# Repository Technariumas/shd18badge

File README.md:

# Science Hack Day Vilnius 2018 - badge

Participant badge for Science Hack Day Vilnius 2018

## Prerequisites

To use the badge, you will need the following:

 * A laptop with Linux, Mac OS or Windows and at least one free USB port.
 * If it’s Windows or Mac OS, make sure to install [drivers](https://wiki.wemos.cc/downloads) for the CH340 UBS2TTL chip.
 * A micro-USB cable with data lines that fits your USB port.
 * You will need a terminal application installed. For Linux and Mac you can use screen, which is installed by default. For Windows we recommend [PuTTy](http://www.chiark.greenend.org.uk/~sgtatham/putty/download.html) or [CoolTerm](http://freeware.the-meiers.org/).
 * Please note that the workshop will be in English.

## Schematics

## Programming

Use dmesg to determine the USB port the badge is connected to, e.g. /dev/ttyUSB0.

Flash the firmware:
cd shd18badge/micropython

Edit the flash_microcontroller.sh file so that it points to the correct USB port. If esptool.py is needed, install it (for example, pip install esptool.py). Then copy the Python files to the microcontroller:

python transfer_files.py -p /dev/ttyUSB5 -b 115200 util.py main.py thermistor.py boot.py
 
## Tutorial
 * A pretty great [tutorial is available here](http://docs.micropython.org/en/latest/esp8266/esp8266/tutorial/index.html)
 * [A MAC user first hand experience](MACUSERS.md) using the badge

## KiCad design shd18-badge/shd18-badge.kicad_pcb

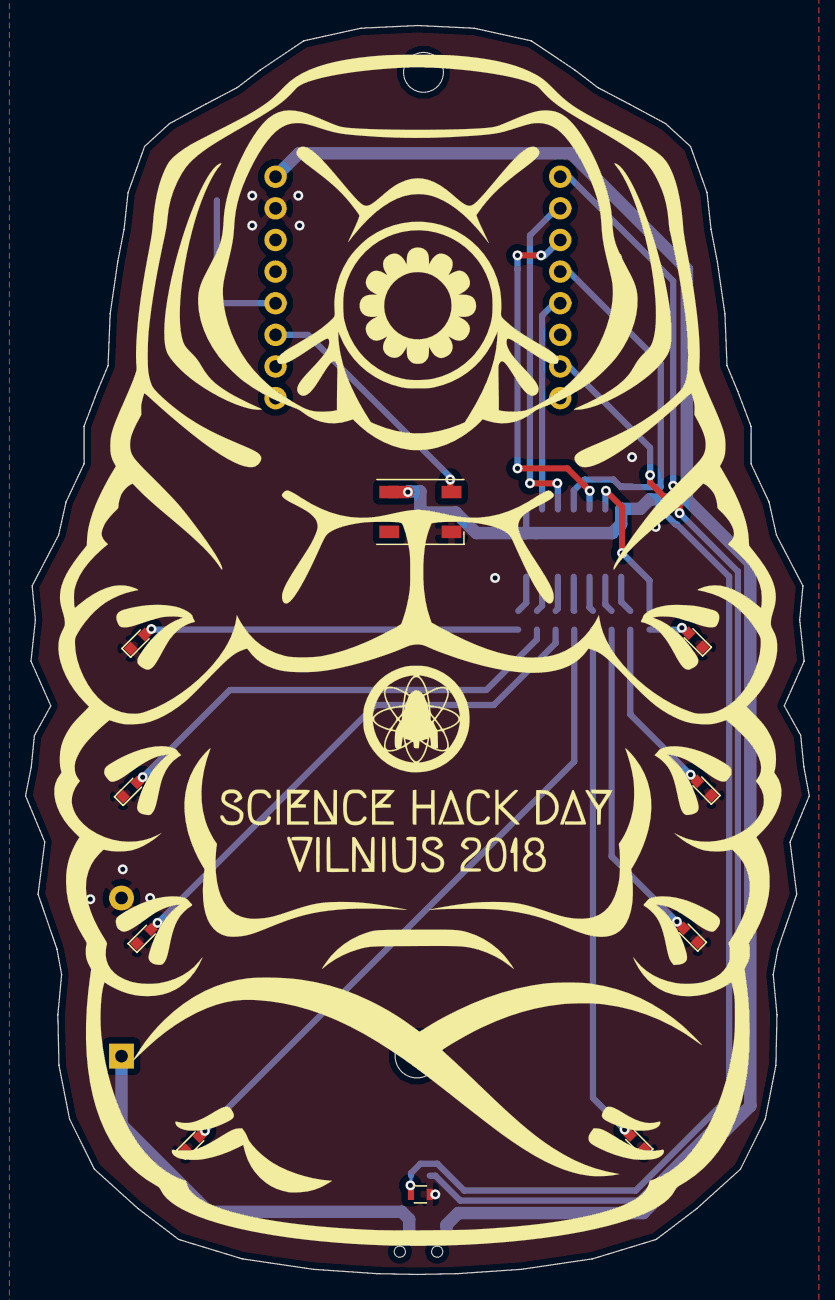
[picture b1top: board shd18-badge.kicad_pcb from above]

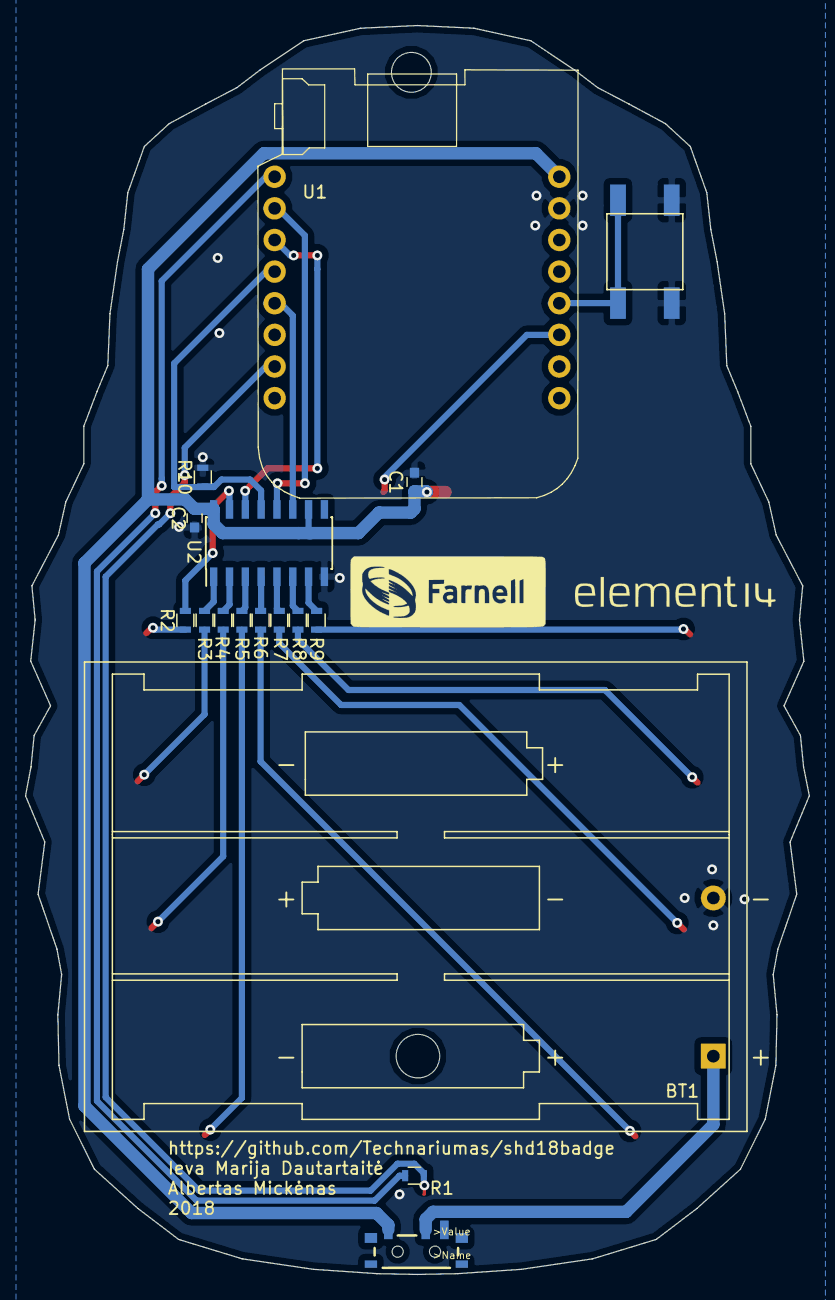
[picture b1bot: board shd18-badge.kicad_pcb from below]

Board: 2 copper layers, 62.9 x 100.3 mm, 28 parts (17 on the bottom side), 27 nets.

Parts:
BT1: Battery; Keystone_2479_3xAAA
C1, C2: 1u; C_0603
D1, D2, D3, D4, D5, D6, D7, D8: LED; LED_0603
LED1: WS2812B; LED_WS2812B-PLCC4
MK1: Mounting_Hole; MountingHole_3.2mm_M3
R1: R; R_0603
R2, R3, R4, R5, R6, R7, R8, R9, R10: 1k; R_0603
SW1: SW_SPDT; SWITCH-SPST-SMD-A
SW2: SW_Push; 4P-SMD-6.2X6.2X4H
TH1: Thermistor; R_0603
U1: WeMos_mini; D1_mini_board
U2: 74HC595; SOIC-16_3.9x9.9mm_Pitch1.27mm

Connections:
+3V3: R1.1, U1.16
GND: BT1.2, C1.2, C2.2, D1.1, D2.1, D3.1, D4.1, D5.1, D6.1, D7.1, D8.1, LED1.3, R10.2, SW2.1, TH1.2, U1.2, U2.8
unnamed: BT1.1, SW1.2
unnamed: D1.2, R9.1
unnamed: D2.2, R8.1
unnamed: D3.2, R7.1
unnamed: D4.2, R6.1
unnamed: D5.2, R5.1
unnamed: D6.2, R4.1
unnamed: D7.2, R3.1
unnamed: D8.2, R2.1
unnamed: LED1.4, U1.6
unnamed: R1.2, TH1.1, U1.10
unnamed: R2.2, U2.15
unnamed: R3.2, U2.1
unnamed: R4.2, U2.2
unnamed: R5.2, U2.3
unnamed: R6.2, U2.4
unnamed: R7.2, U2.5
unnamed: R8.2, U2.6
unnamed: R9.2, U2.7
unnamed: R10.1, U1.13, U2.13
unnamed: SW2.2, U1.5
unnamed: U1.12, U2.11
unnamed: U1.14, U2.14
unnamed: U1.15, U2.12
VCC: C1.1, C2.1, LED1.1, SW1.3, U1.1, U2.10, U2.16

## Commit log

2018-01-10 Add some text to README, add schematics
2018-01-10 Add initial micropython files - image and a ws2812 test script, also utilities for flashing
2018-01-29 Add links to helper apps and drivers
2018-02-05 Fix the upload script, add more blinking
2018-02-06 Add thermistor conversion to temperature, disable networking on boot
2018-02-06 Add some effects
2018-02-06 Remove emtpy file
2018-02-06 Add afterboot effects
2018-02-06 Readme
2018-02-10 add all the rest
2018-02-10 Create MACUSERS.md
    guidelines for a mac user including some programming tips
